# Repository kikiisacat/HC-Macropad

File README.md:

# HC-Macropad
A custom 15-key/2-dial/oled macropad. It will be put to good use to open programs, run complex commands, and execute multi-step actions.
# Why I made it
I wanted to learn PCB design basics. I also wanted many custom keys for productivity, and chose this 2-dial and 15-key layout for this reason. I chose to use a MCP23017 to get access to more than 8 inputs.
# Parts
Seeed Studio Xiao RP2040
15 Switches
2 EC11E Rotary Encoders that also act as buttons
0.91 in OLED
16 SK6812 MINI-E RGB LEDs, 15 for keys, 1 for status/additional
MCP23017 for more inputs
74AHCT125 for LED buffer

# Dimensions
100 x 90.5mm, Two layers
6 Mounting holes, 2.2mm diameter each.

# Use
Just connect a cable and install the firmware, and then start assigning key functions.

# Images

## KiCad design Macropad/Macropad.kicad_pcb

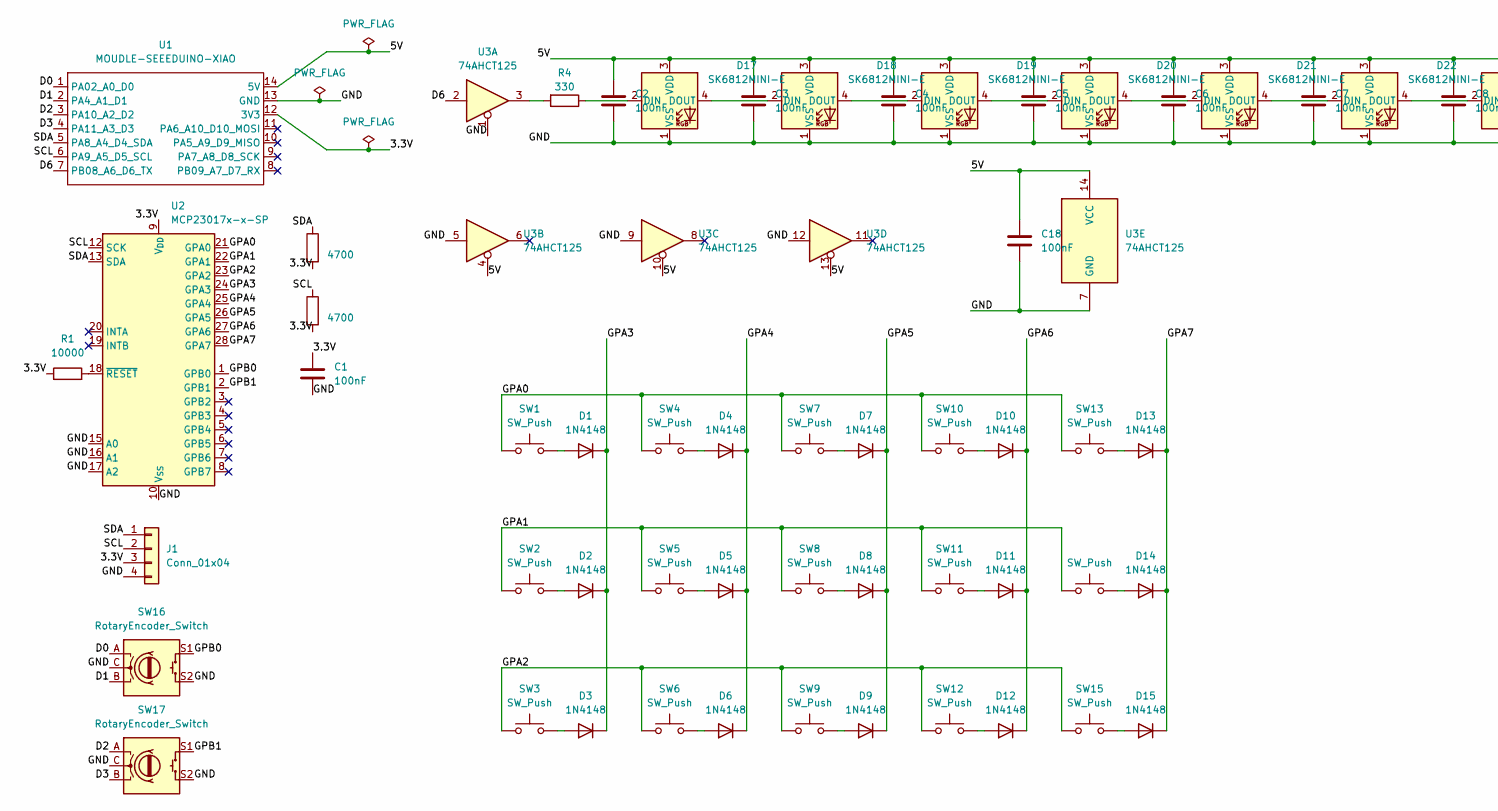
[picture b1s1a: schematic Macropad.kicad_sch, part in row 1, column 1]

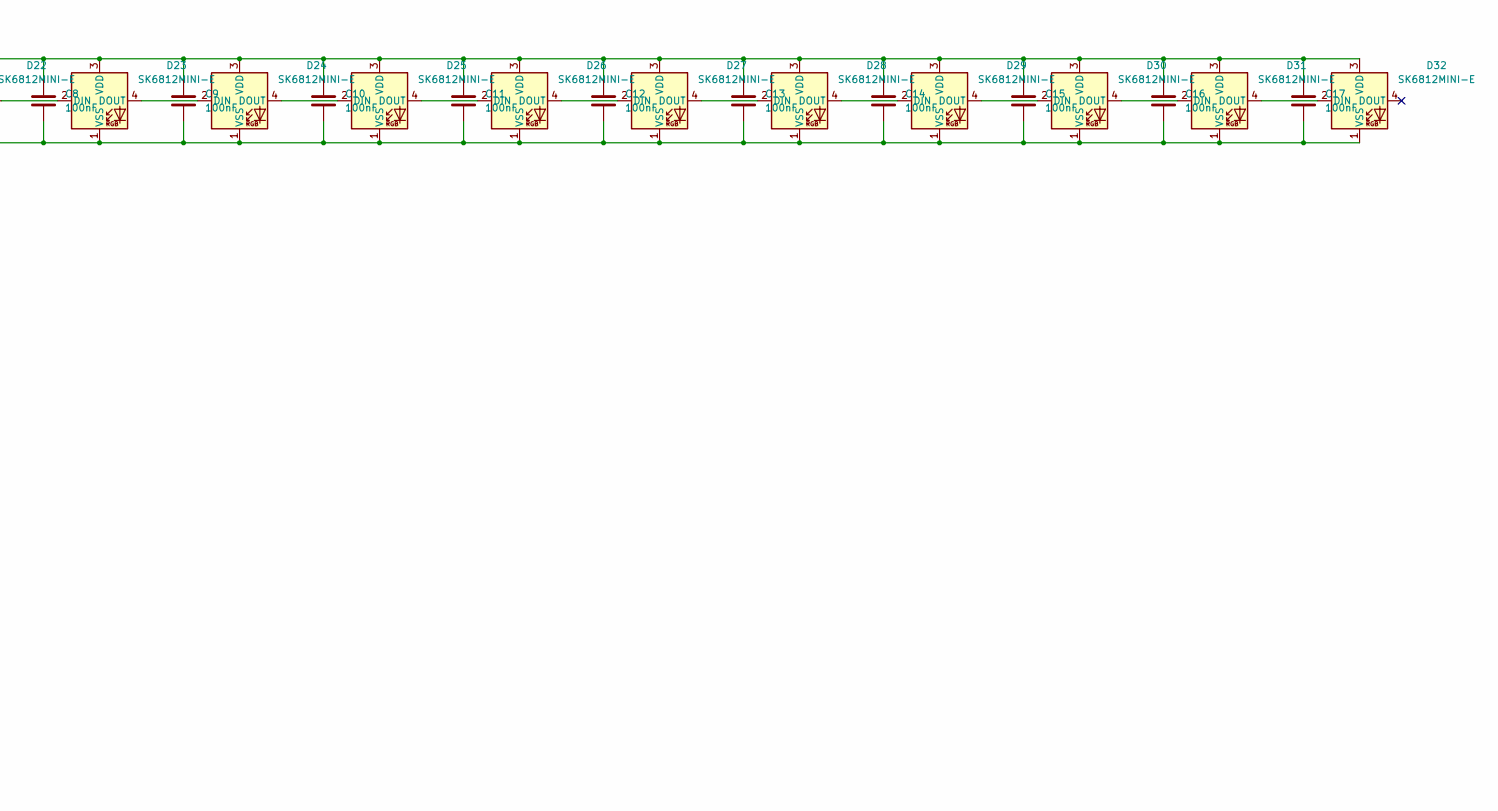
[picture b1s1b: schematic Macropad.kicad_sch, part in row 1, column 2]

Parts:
C1, C2, C3, C4, C5, C6, C7, C8, C9, C10, C11, C12, C13, C14, C15, C16, C17, C18: 100nF; C_0805_2012Metric
D1, D2, D3, D4, D5, D6, D7, D8, D9, D10, D11, D12, D13, D14, D15: 1N4148; D_DO-35_SOD27_P7.62mm_Horizontal
D17, D18, D19, D20, D21, D22, D23, D24, D25, D26, D27, D28, D29, D30, D31, D32: SK6812MINI-E; LED_SK6812MINI-E_3.2x2.8mm_P1.5mm_ReverseMount
J1: Conn_01x04; PinHeader_1x04_P2.54mm_Vertical
R1: 10000; R_0805_2012Metric
R2, R3: 4700; R_0805_2012Metric
R4: 330; R_0805_2012Metric
SW1, SW2, SW3, SW4, SW5, SW6, SW7, SW8, SW9, SW10, SW11, SW12, SW13, SW14, SW15: SW_Push; SW_Cherry_MX_1.00u_PCB
SW16, SW17: RotaryEncoder_Switch; RotaryEncoder_Alps_EC11E-Switch_Vertical_H20mm
U1: MOUDLE-SEEEDUINO-XIAO; XIAO-Generic-Hybrid-14P-2.54-21X17.8MM
U2: MCP23017x-x-SP; DIP-28_W7.62mm
U3: 74AHCT125; DIP-14_W7.62mm

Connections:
/3.3V: C1.1, J1.3, R1.1, R2.2, R3.2, U1.12 (3V3), U2.9 (V_{DD})
/5V: C2.1, C3.1, C4.1, C5.1, C6.1, C7.1, C8.1, C9.1, C10.1, C11.1, C12.1, C13.1, C14.1, C15.1, C16.1, C17.1, C18.1, D17.3 (VDD), D18.3 (VDD), D19.3 (VDD), D20.3 (VDD), D21.3 (VDD), D22.3 (VDD), D23.3 (VDD), D24.3 (VDD), D25.3 (VDD), D26.3 (VDD), D27.3 (VDD), D28.3 (VDD), D29.3 (VDD), D30.3 (VDD), D31.3 (VDD), D32.3 (VDD), U1.14 (5V), U3.4, U3.10, U3.13, U3.14 (VCC)
/D0: SW16.A, U1.1 (PA02_A0_D0)
/D1: SW16.B, U1.2 (PA4_A1_D1)
/D2: SW17.A, U1.3 (PA10_A2_D2)
/D3: SW17.B, U1.4 (PA11_A3_D3)
/D6: U1.7 (PB08_A6_D6_TX), U3.2
/GND: C1.2, C2.2, C3.2, C4.2, C5.2, C6.2, C7.2, C8.2, C9.2, C10.2, C11.2, C12.2, C13.2, C14.2, C15.2, C16.2, C17.2, C18.2, D17.1 (VSS), D18.1 (VSS), D19.1 (VSS), D20.1 (VSS), D21.1 (VSS), D22.1 (VSS), D23.1 (VSS), D24.1 (VSS), D25.1 (VSS), D26.1 (VSS), D27.1 (VSS), D28.1 (VSS), D29.1 (VSS), D30.1 (VSS), D31.1 (VSS), D32.1 (VSS), J1.4, SW16.C, SW16.S2, SW17.C, SW17.S2, U1.13 (GND), U2.10 (V_{SS}), U2.15 (A0), U2.16 (A1), U2.17 (A2), U3.1, U3.5, U3.7 (GND), U3.9, U3.12
/GPA0: SW1.1, SW4.1, SW7.1, SW10.1, SW13.1, U2.21 (GPA0)
/GPA1: SW2.1, SW5.1, SW8.1, SW11.1, SW14.1, U2.22 (GPA1)
/GPA2: SW3.1, SW6.1, SW9.1, SW12.1, SW15.1, U2.23 (GPA2)
/GPA3: D1.1 (K), D2.1 (K), D3.1 (K), U2.24 (GPA3)
/GPA4: D4.1 (K), D5.1 (K), D6.1 (K), U2.25 (GPA4)
/GPA5: D7.1 (K), D8.1 (K), D9.1 (K), U2.26 (GPA5)
/GPA6: D10.1 (K), D11.1 (K), D12.1 (K), U2.27 (GPA6)
/GPA7: D13.1 (K), D14.1 (K), D15.1 (K), U2.28 (GPA7)
/GPB0: SW16.S1, U2.1 (GPB0)
/GPB1: SW17.S1, U2.2 (GPB1)
/SCL: J1.2, R3.1, U1.6 (PA9_A5_D5_SCL), U2.12 (SCK)
/SDA: J1.1, R2.1, U1.5 (PA8_A4_D4_SDA), U2.13 (SDA)
unnamed: D1.2 (A), SW1.2
unnamed: D2.2 (A), SW2.2
unnamed: D3.2 (A), SW3.2
unnamed: D4.2 (A), SW4.2
unnamed: D5.2 (A), SW5.2
unnamed: D6.2 (A), SW6.2
unnamed: D7.2 (A), SW7.2
unnamed: D8.2 (A), SW8.2
unnamed: D9.2 (A), SW9.2
unnamed: D10.2 (A), SW10.2
unnamed: D11.2 (A), SW11.2
unnamed: D12.2 (A), SW12.2
unnamed: D13.2 (A), SW13.2
unnamed: D14.2 (A), SW14.2
unnamed: D15.2 (A), SW15.2
unnamed: D17.2 (DIN), R4.1
unnamed: D17.4 (DOUT), D18.2 (DIN)
unnamed: D18.4 (DOUT), D19.2 (DIN)
unnamed: D19.4 (DOUT), D20.2 (DIN)
unnamed: D20.4 (DOUT), D21.2 (DIN)
unnamed: D21.4 (DOUT), D22.2 (DIN)
unnamed: D22.4 (DOUT), D23.2 (DIN)
unnamed: D23.4 (DOUT), D24.2 (DIN)
unnamed: D24.4 (DOUT), D25.2 (DIN)
unnamed: D25.4 (DOUT), D26.2 (DIN)
unnamed: D26.4 (DOUT), D27.2 (DIN)
unnamed: D27.4 (DOUT), D28.2 (DIN)
unnamed: D28.4 (DOUT), D29.2 (DIN)
unnamed: D29.4 (DOUT), D30.2 (DIN)
unnamed: D30.4 (DOUT), D31.2 (DIN)
unnamed: D31.4 (DOUT), D32.2 (DIN)
unnamed: R4.2, U3.3
unnamed: R1.2, U2.18 (~RESET)

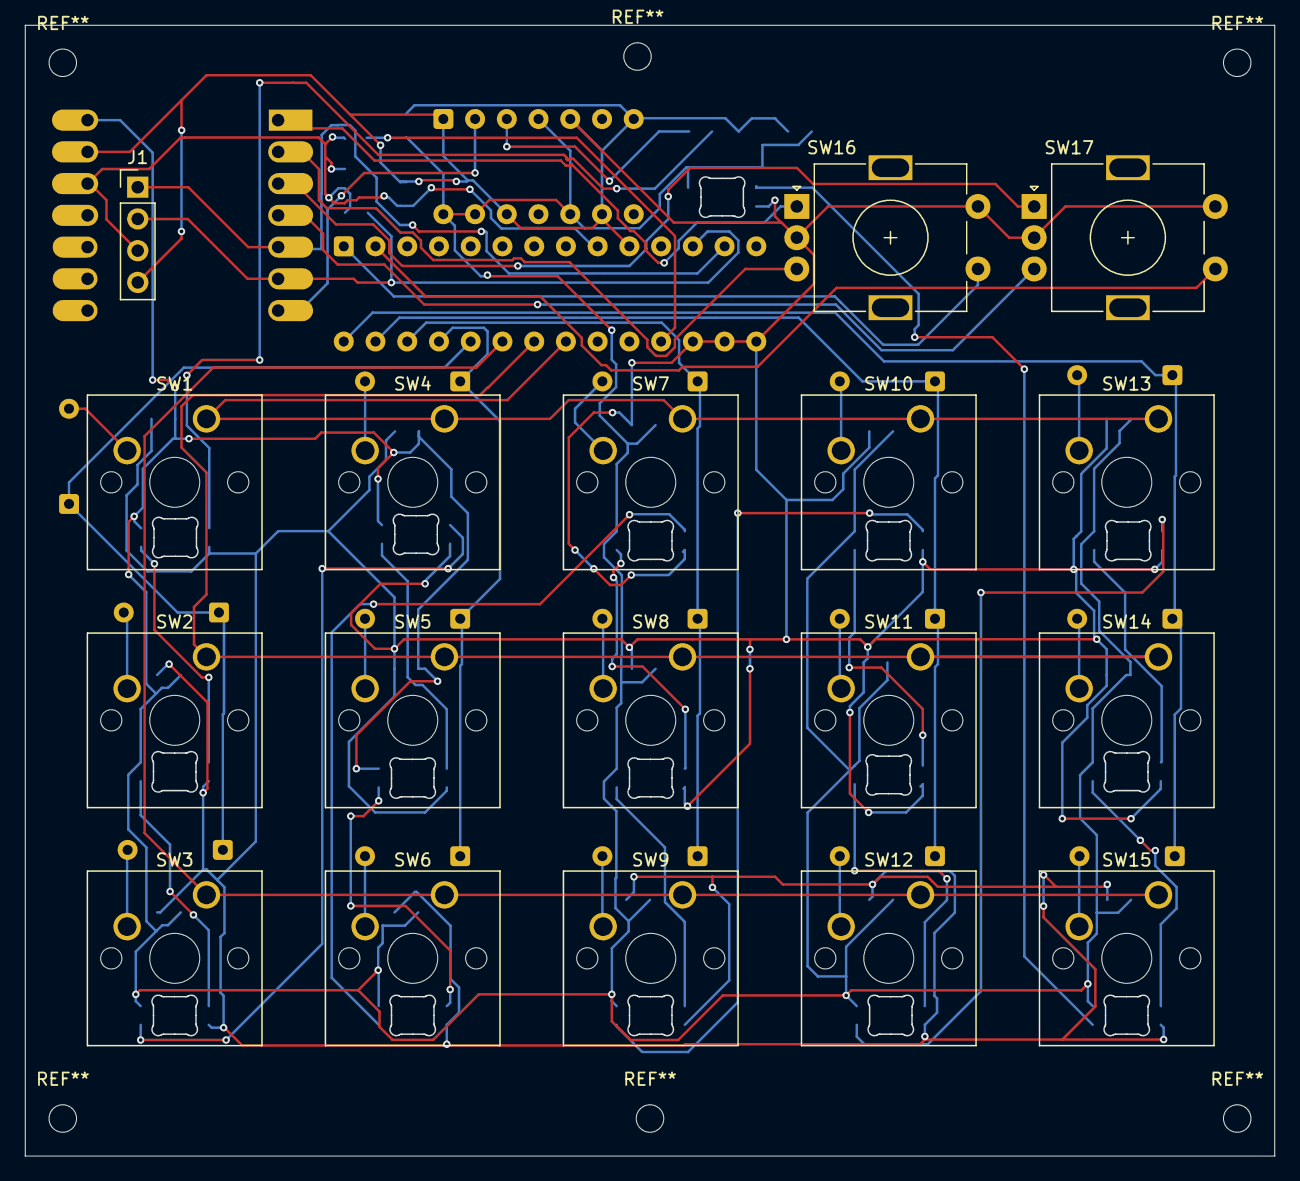
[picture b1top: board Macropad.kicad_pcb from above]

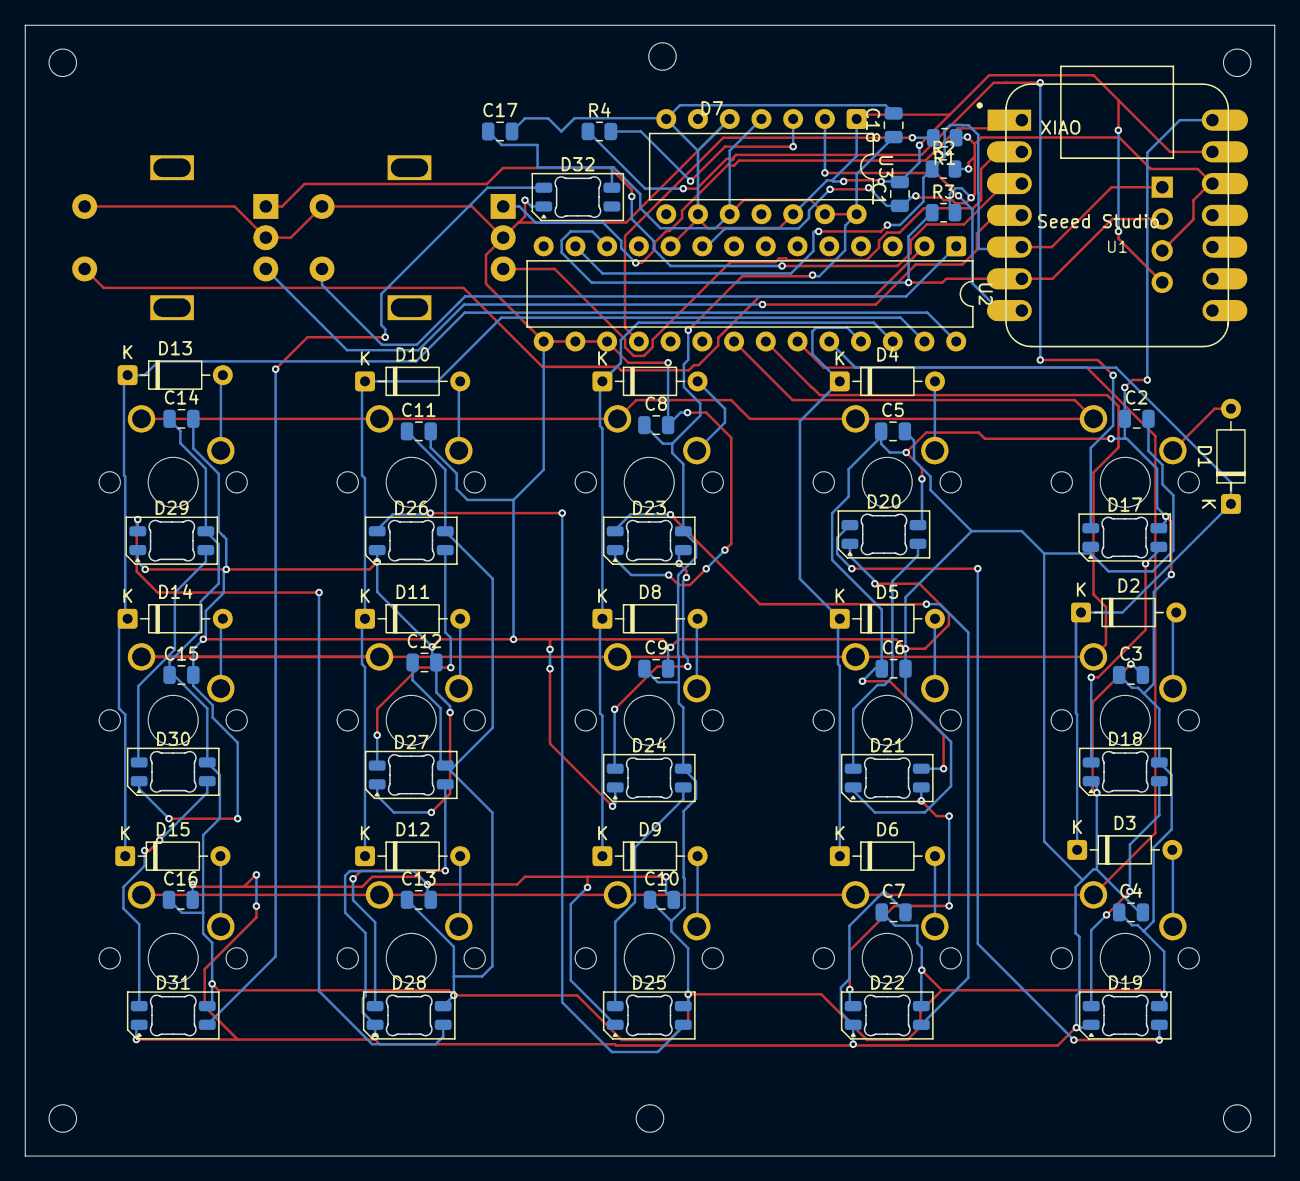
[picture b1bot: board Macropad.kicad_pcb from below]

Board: 2 copper layers, 100.0 x 90.5 mm, 74 parts (56 on the bottom side), 53 nets.
